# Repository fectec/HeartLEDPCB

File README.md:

# Heart LED PCB

<p align="justify">A collection of <b>Valentine's Day-themed PCB designs</b> featuring LED animations in the shape of a heart. Perfect for pendants or keyrings!</p>

## Main Branch

<p align="justify">The main branch features a design built around the <b>ICM7555</b> timer IC, configured in astable operation mode. The timer output drives a <b>CD4017B</b> decade counter, which sequences through LEDs to create an animated pattern. Power is supplied by a <b>CR2032</b> 3 V battery through a <b>TPS6122</b> boost converter.</p>

### Components Overview

#### ICM7555IBAZ-T

<p align="justify">The ICM7555 is a CMOS RC timer that provides significantly improved performance over the standard SE/NE 555/556 and 355 timers. It is a direct replacement for these devices in most applications. Enhanced features include low supply current (<i>60 μA</i>), a wide operating supply voltage range (<i>2V to 18V</i>), higher frequency performance, and no requirement to decouple the Control Voltage pin for stable operation.</p> 

<p align="justify">Although the ICM7555 itself consumes very little current, the total system supply current can increase unless high-impedance timing components are used. To address this, a high value for R and a low value for C were selected.</p> 

<p align="justify">The frequency of the astable operation is determined by the formula:</p> 

<div align="center">
	
$`f=\frac{1}{RC}`$

</div>

<p align="justify">To achieve a period of approximately one second, R was set to <i>100 kΩ</i> and C to <i>4.7 μF</i>.</p> 

#### CD4017BM96

<p align="justify">The CD4017B is a decade counter with 10 decoded outputs. Each output remains high for the duration of one full clock cycle, sequentially cycling through the outputs with each clock pulse. It operates over a wide supply voltage range of <i>3V to 18V</i>, making it compatible with various applications.</p>

#### TPS61222DCKR

<p align="justify">The TPS6122x family devices provide a power-supply solution for products powered by single-cell, two-cell, or three-cell alkaline, NiCd, or NiMH batteries, or a single-cell Li-Ion or Li-polymer battery. They offer up to 95% efficiency under typical operating conditions.</p>

<p align="justify">In this design, the specific application of the device is a fixed output voltage supply of <i>5 V at up to 60 mA</i>. The TPS61222 DC/DC converter is suitable for systems powered by a total typical input voltage between 0.7 V and 5.5 V.</p>

<p align="justify">In the fixed-voltage version, the output is set by an internal resistor divider. To ensure proper operation, a suitable inductor must be connected between pin VIN and pin L. Inductor values of <i>4.7 μH</i> provide good performance across the full input and output voltage range. Using inductor values below 2.2 μH is not recommended.</p>

<p align="justify">An input capacitor with a value of at least <i>10 μF</i> is recommended to improve the transient behavior of the regulator and reduce EMI in the total power supply circuit. A ceramic capacitor placed as close as possible to the VIN and GND pins of the IC is advised.</p>

<p align="justify">For the output capacitor (C2), small ceramic capacitors are recommended, placed as close as possible to the VOUT and GND pins of the IC. A minimum capacitance value of 4.7 μF should be used; <i>10 μF</i> is preferred.</p>

### BOM & Schematic Diagram

| Component   | Value/Model        | Qty | LCSC #      | Notes                          |
|-------------|--------------------|-----|-------------|--------------------------------|
| BT1         | Keystone 1060      | 1   | C5370859    | CR2032 holder                  |
| C1          | 4.7 µF             | 1   | C1705       | ICM7555 capacitor              | 
| C2, C3      | 10 µF              | 2   | C1691       | TPS61222 Input/output caps     |
| L1          | 4.7 µH             | 1   | C576538     | LQH3NPN series                 |
| R1          | 100 kΩ             | 1   | C15458      | Timer RC network               |
| R2          | 10 kΩ              | 1   | C25531      | Timer RC network               |
| R3-R12      | 3.3 kΩ             | 10  | C25936      | LED current limit              |
| U1          | ICM7555IBAZ-T      | 1   | C357816     | CMOS timer                     |
| U2          | CD4017BM96         | 1   | C11349      | Decade counter                 |
| U3          | TPS61222DCKR       | 1   | C116461     | Boost converter                |
| U4          | HX SS12F44G4       | 1   | C5149844    | Power switch                   |
| TP1-TP3     | 1.0 mm             | 3   | -           | Test points                    |

## HT7750A Branch

<p align="justify">In this branch, the TPS61222DCKR converter is replaced by the <b>HT7750A</b>. The HT77XXA series is a family of step-up DC/DC converters known for their high efficiency and low ripple. These converters feature an extremely low start-up voltage and high output voltage accuracy. They require only three external components to provide a fixed output voltage of 2.7 V, 3.0 V, 3.3 V, or <i>5.0 V</i>.</p>

### BOM & Schematic Diagram

| Component   | Value/Model        | Qty | LCSC #      | Notes                          |
|-------------|--------------------|-----|-------------|--------------------------------|
| BT1         | Keystone 1060      | 1   | C5370859    | CR2032 holder                  |
| C1          | 4.7 µF             | 1   | C1705       | ICM7555 capacitor              | 
| C2          | 47 µF (Tantalum)   | 1   | C7190       | HT7750A input capacitor        |
| C3          | 22 µF (Tantalum)   | 1   | C7183       | HT7750A output capacitor       |
| L1          | 47-100 µH          | 1   | C1034       | HT7750A inductor               |
| S1          | 1N5817             | 1   | C727113     | HT7750A schottky diode         |
| R1          | 100 kΩ             | 1   | C15458      | Timer RC network               |
| R2          | 10 kΩ              | 1   | C25531      | Timer RC network               |
| R3-R12      | 3.3 kΩ             | 10  | C25936      | LED current limit              |
| U1          | ICM7555IBAZ-T      | 1   | C357816     | CMOS timer                     |
| U2          | CD4017BM96         | 1   | C11349      | Decade counter                 |
| U3          | HT7750A            | 1   | C25988      | Boost converter                |
| U4          | HX SS12F44G4       | 1   | C5149844    | Power switch                   |
| TP1-TP3     | 1.0 mm             | 3   | -           | Test points                    |

## MCU Branch

<p align="justify">This branch replaces the timer and decade counter with an <b>ATtiny816</b> microcontroller. The ATtiny816 is a member of the tinyAVR® 1-series family featuring advanced analog features and core independent peripherals. This design allows for more sophisticated LED control and animations through programmable patterns.</p>

<p align="justify">Programming is accomplished via the Unified Program and Debug Interface (<i>UPDI</i>), a one-wire interface for external programming and debugging. The circuit incorporates a tactile button connected to a GPIO pin for user interaction.</p>

### BOM & Schematic Diagram

| Component   | Value/Model        | Qty | LCSC #      | Notes                          |
|-------------|--------------------|-----|-------------|--------------------------------|
| BT1         | CR2032-BS-6-1      | 1   | C70377      | CR2032 holder                  |
| C1          | 100 nF             | 2   | C301918     | MCU decoupling capacitors      |
| C2          | 100 nF             | 2   | C301918     | Button debounce capacitor      |
| D1          | LED (Blue)         | 1   | C7496819    | Status LED                     |
| D2-D10      | LED (Red)          | 9   | C7496820    | Animation LEDs                 |
| J1          | 1x03 2.54 mm       | 1   | -           | UPDI programming header        |
| R1-R11      | 1 kΩ               | 11  | C25543      | LED current limit              |
| SW1         | TS-1187A-B-A-B     | 1   | C318884     | Tactile switch                 |
| U1          | HX SS12F44G4       | 1   | C5149844    | Power switch                   |
| U2          | ATTINY816-MN       | 1   | C617908     | Main MCU                       |
| TP1         | 1.5 mm             | 1   | -           | Test point                     |

## Simple NE555 Branch

<p align="justify">Finally, this branch replaces the ICM7555 timer IC with a conventional <b>NE555</b>, offering a cost-effective alternative that requires only one SMD component - the IC itself. This design imitates a popular DIY kit, where the NE555 generates a <i>1 Hz signal</i> at pin 3, alternating between high and low levels. When pin 3 is low, the upper row of LEDs illuminates, and when high, the bottom row lights up instead, creating an appealing visual effect.</p>

<p align="justify">While the circuit can operate with a CR2032 3V battery, one LED row will appear dimmer due to the NE555's minimum voltage requirements. For optimal brightness across both rows, a 5V power supply connector can be soldered to the board as an alternative power source.</p>

### BOM & Schematic Diagram

| Component   | Value/Model                    | Qty | Notes                          |
|-------------|--------------------------------|-----|--------------------------------|
| U1          | NE555DR                        | 1   | RC Timer                       |
| U2          | 1066                           | 1   | CR2032 holder                  |
| SW1         | SS12D00G3                      | 1   | Power switch                   |
| D1-D10      | LED 3.00 mm                    | 10  | LEDs                           |
| R1-R10      | 1 kΩ 6.3 x 2.5 x 7.62 mm       | 10  | LED current limit              |
| R11-R12     | 10 kΩ 6.3 x 2.5 x 7.62 mm      | 2   | Timer RC network               |
| C1          | 47 µF 5.00 x 7.00 x 2.00 mm    | 1   | NE555 capacitor                |
| J1          | 1x02 2.54 mm                   | 1   | Power supply header            |

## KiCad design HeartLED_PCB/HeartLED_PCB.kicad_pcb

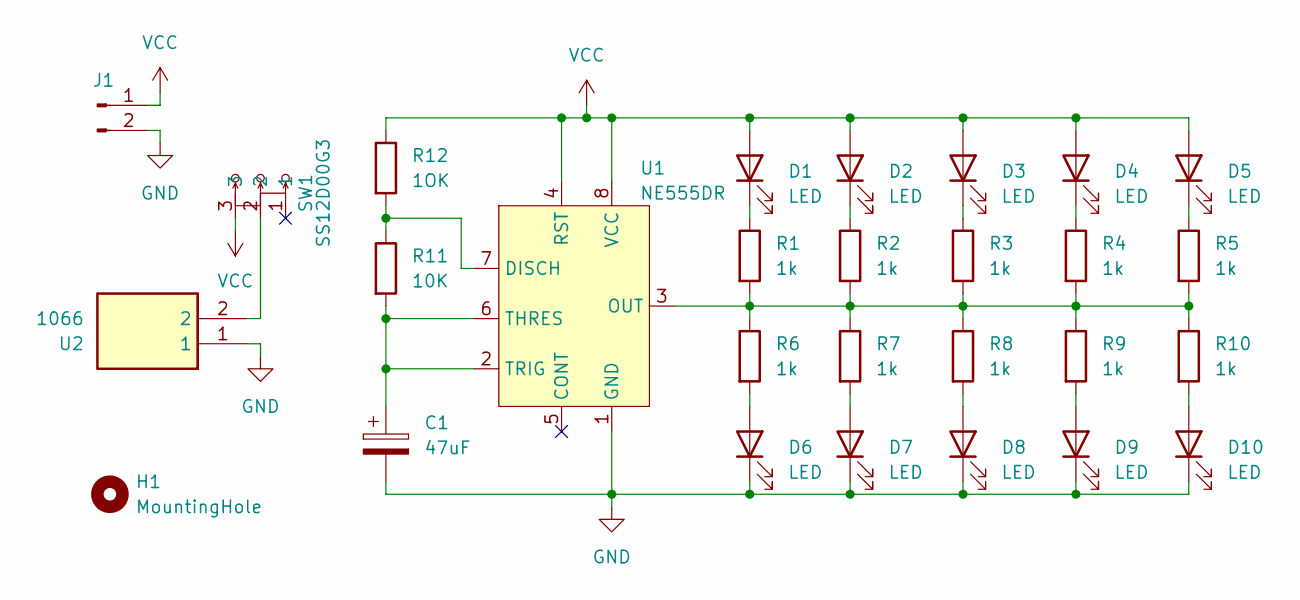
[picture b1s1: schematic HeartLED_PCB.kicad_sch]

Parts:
C1: 47uF; C_Radial_D5.0mm_H7.0mm_P2.00mm
D1, D2, D3, D4, D5, D6, D7, D8, D9, D10: LED; LED_D3.0mm
H1: MountingHole; MountingHole_2.7mm
J1: Conn_01x02_Pin; PinHeader_1x02_P2.54mm_Vertical
R1, R2, R3, R4, R5, R6, R7, R8, R9, R10: 1k; R_Axial_DIN0207_L6.3mm_D2.5mm_P7.62mm_Horizontal
R11: 10K; R_Axial_DIN0207_L6.3mm_D2.5mm_P7.62mm_Horizontal
R12: 1OK; R_Axial_DIN0207_L6.3mm_D2.5mm_P7.62mm_Horizontal
SW1: SS12D00G3; LCSC Part C9900018735
U1: NE555DR; LCSC Part C7593
U2: 1066; Mouser Part Number 534-1066

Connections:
GND: C1.2, D6.1 (K), D7.1 (K), D8.1 (K), D9.1 (K), D10.1 (K), J1.2, U1.1 (GND), U2.1
unnamed: D1.1 (K), R1.1
unnamed: D2.1 (K), R2.1
unnamed: D3.1 (K), R3.1
unnamed: D4.1 (K), R4.1
unnamed: D5.1 (K), R5.1
unnamed: D6.2 (A), R6.2
unnamed: D7.2 (A), R7.2
unnamed: D8.2 (A), R8.2
unnamed: D9.2 (A), R9.2
unnamed: D10.2 (A), R10.2
unnamed: SW1.2, U2.2
unnamed: R11.1, R12.2, U1.7 (DISCH)
unnamed: R1.2, R2.2, R3.2, R4.2, R5.2, R6.1, R7.1, R8.1, R9.1, R10.1, U1.3 (OUT)
unnamed: C1.1, R11.2, U1.2 (TRIG), U1.6 (THRES)
VCC: D1.2 (A), D2.2 (A), D3.2 (A), D4.2 (A), D5.2 (A), J1.1, R12.1, SW1.3, U1.4 (RST), U1.8 (VCC)

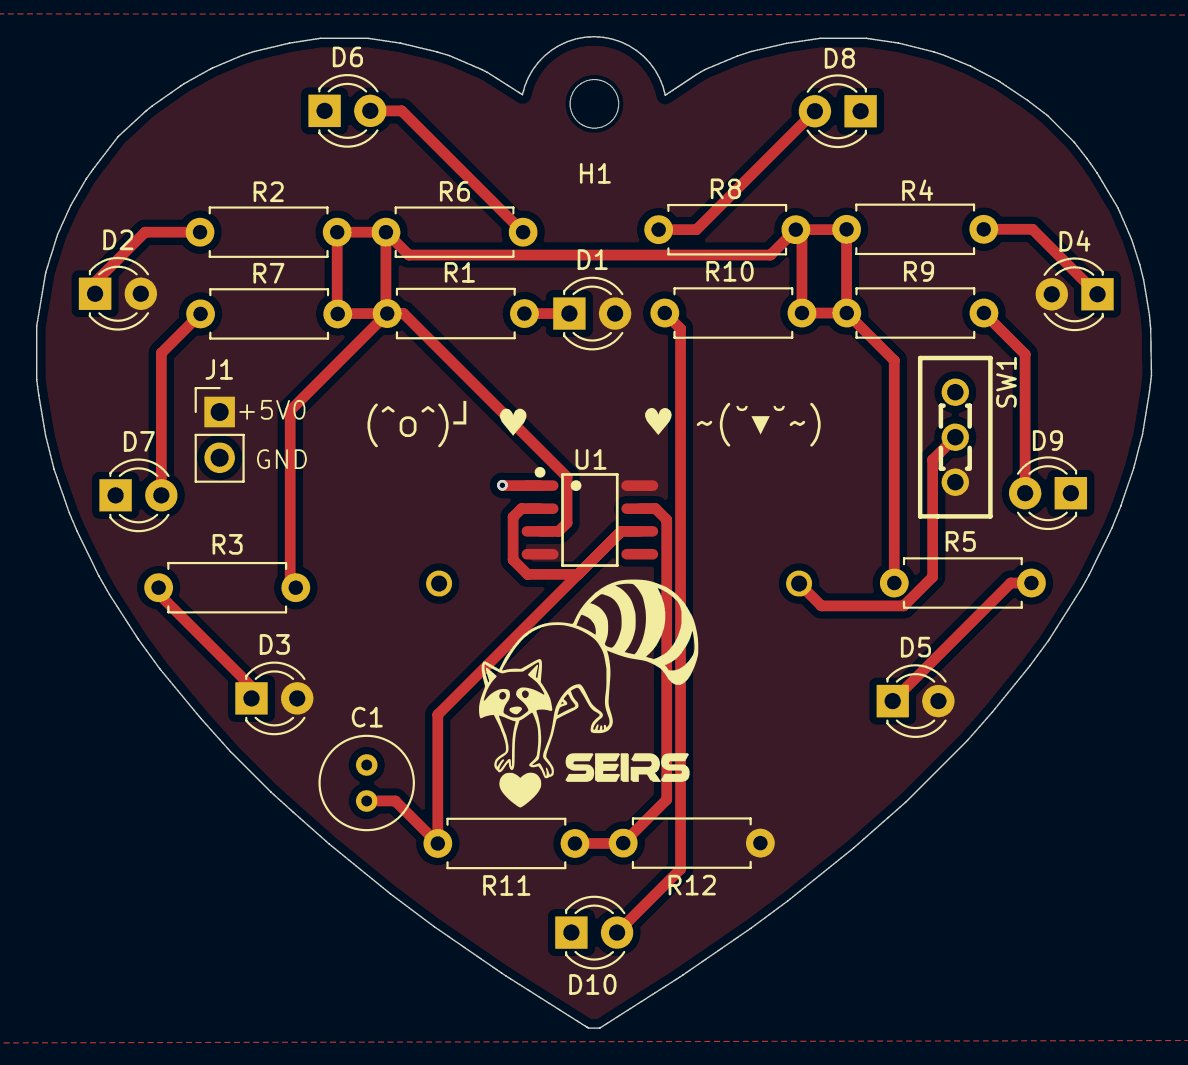
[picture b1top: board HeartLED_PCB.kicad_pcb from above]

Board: 2 copper layers, 61.9 x 55.1 mm, 28 parts (1 on the bottom side), 16 nets.

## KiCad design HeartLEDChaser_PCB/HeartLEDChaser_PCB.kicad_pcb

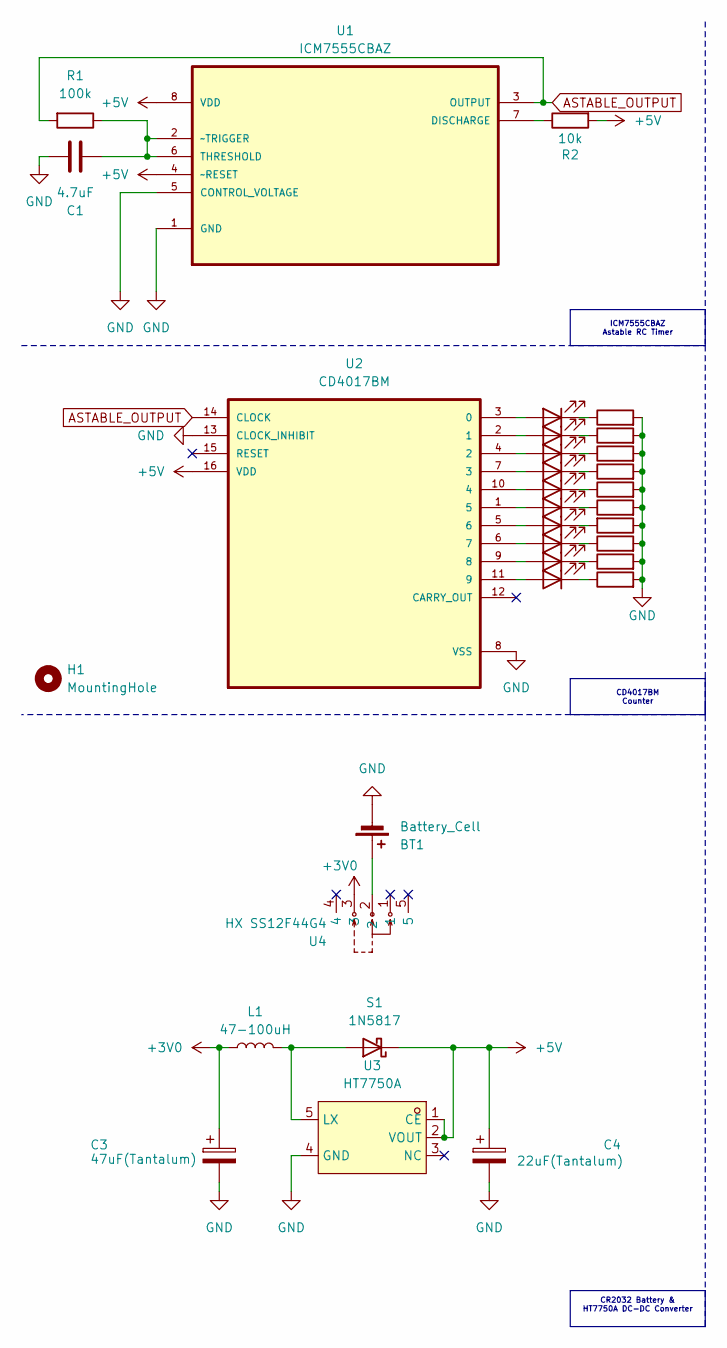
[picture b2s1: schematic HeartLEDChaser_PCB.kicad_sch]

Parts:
BT1: Battery_Cell; BatteryHolder_Keystone_1060_1x2032
C1: 4.7uF; CL10A475KP8NNNC
C3: 47uF(Tantalum); TAJA476K006RNJ
C4: 22uF(Tantalum); TAJA476K006RNJ
D1, D2, D3, D4, D5, D6, D7, D8, D9, D10: LED; LED_D3.0mm
H1: MountingHole; MountingHole_2.1mm
L1: 47-100uH; SDFL1608Q4R7KTF
R1: 100k; 0603WAJ0104T5E
R2: 10k; 0402WGJ0103TCE
R3, R4, R5, R6, R7, R8, R9, R10, R11, R12: 3.3k; 0402WGJ0332TCE
S1: 1N5817; 1N5817W
U1: ICM7555CBAZ; MPN ICM7555CBAZ
U2: CD4017BM
U3: HT7750A; LCSC Part C259884
U4: HX SS12F44G4; LCSC Part C5149844

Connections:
+3V0: C3.1, L1.1, U4.3
+5V: C4.1, R2.2, S1.1 (K), U1.4 (~RESET), U1.8 (VDD), U2.16 (VDD), U3.1 (CE), U3.2 (VOUT)
ASTABLE_OUTPUT: R1.2, U1.3 (OUTPUT), U2.14 (CLOCK)
GND: BT1.2 (-), C1.2, C3.2, C4.2, R3.2, R4.2, R5.2, R6.2, R7.1, R8.2, R9.2, R10.2, R11.2, R12.2, U1.1 (GND), U1.5 (CONTROL_VOLTAGE), U2.8 (VSS), U2.13 (CLOCK_INHIBIT), U3.4 (GND)
unnamed: BT1.1 (+), U4.2
unnamed: D1.2 (A), U2.1 (5)
unnamed: D1.1 (K), R3.1
unnamed: D2.2 (A), U2.2 (1)
unnamed: D2.1 (K), R4.1
unnamed: D3.2 (A), U2.3 (0)
unnamed: D3.1 (K), R5.1
unnamed: D4.2 (A), U2.4 (2)
unnamed: D4.1 (K), R6.1
unnamed: D5.2 (A), U2.5 (6)
unnamed: D5.1 (K), R7.2
unnamed: D6.2 (A), U2.6 (7)
unnamed: D6.1 (K), R8.1
unnamed: D7.2 (A), U2.7 (3)
unnamed: D7.1 (K), R9.1
unnamed: D8.2 (A), U2.9 (8)
unnamed: D8.1 (K), R10.1
unnamed: D9.2 (A), U2.10 (4)
unnamed: D9.1 (K), R11.1
unnamed: D10.2 (A), U2.11 (9)
unnamed: D10.1 (K), R12.1
unnamed: L1.2, S1.2 (A), U3.5 (LX)
unnamed: R2.1, U1.7 (DISCHARGE)
unnamed: C1.1, R1.1, U1.2 (~TRIGGER), U1.6 (THRESHOLD)

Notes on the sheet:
CR2032 Battery & HT7750A DC-DC Converter
CD4017BM Counter
ICM7555CBAZ Astable RC Timer

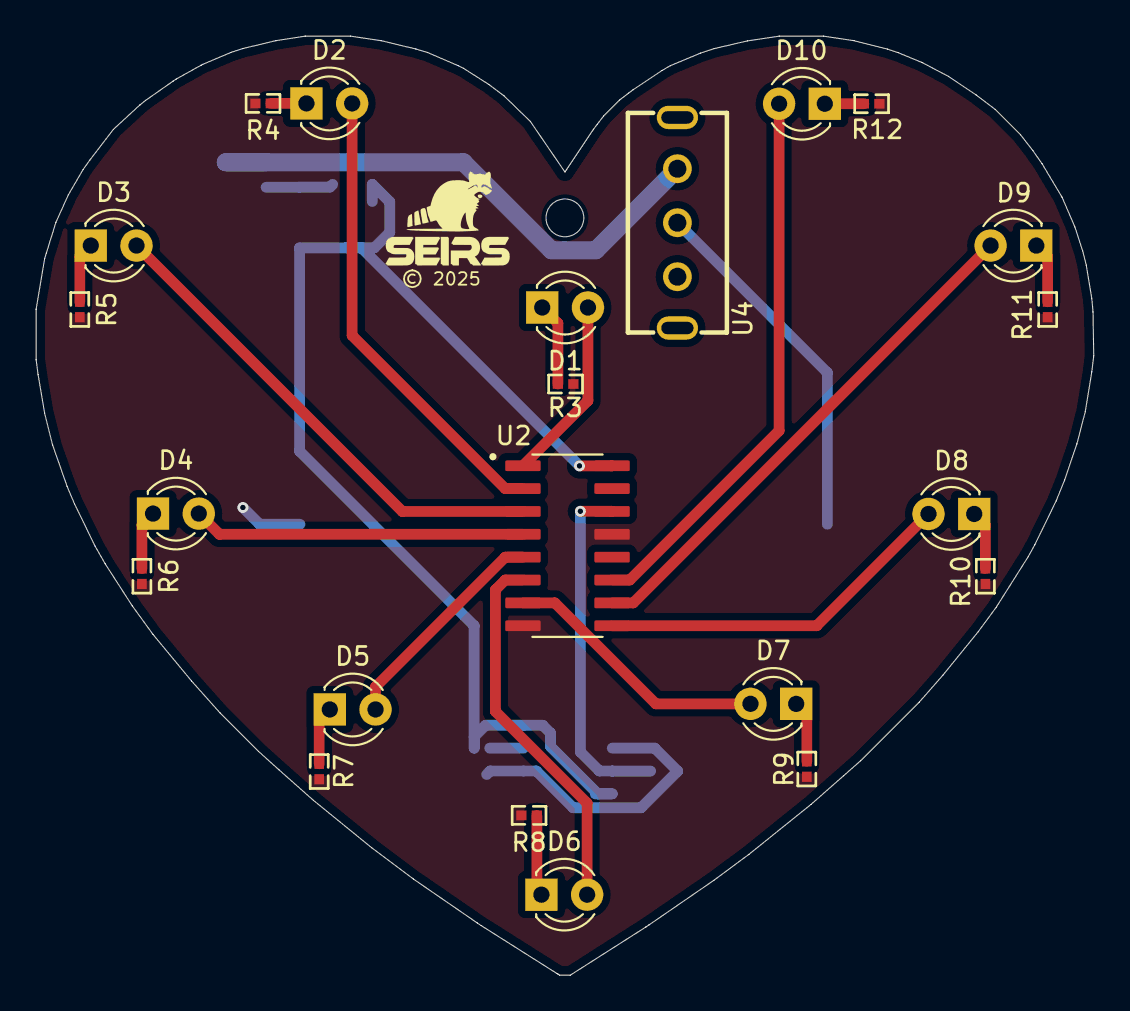
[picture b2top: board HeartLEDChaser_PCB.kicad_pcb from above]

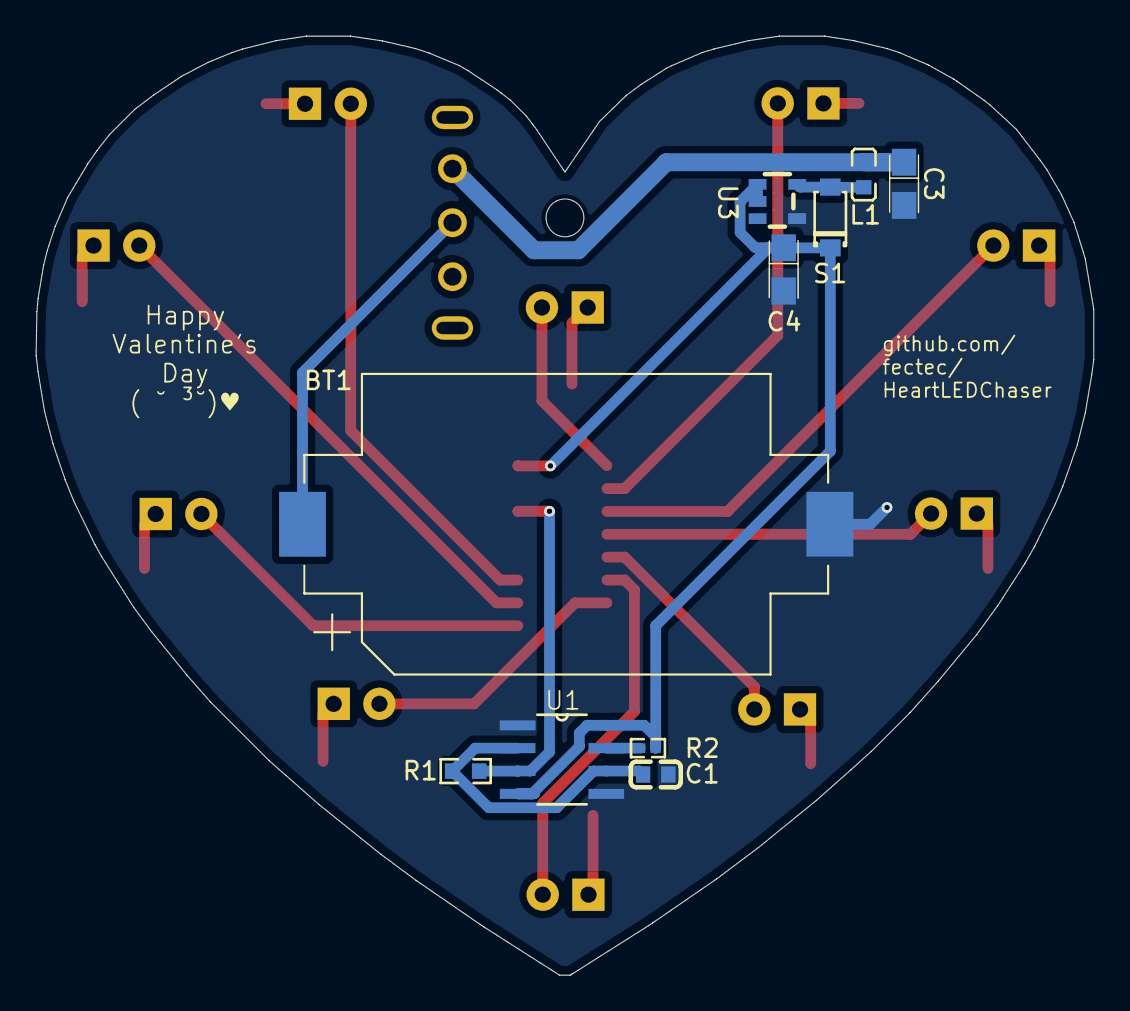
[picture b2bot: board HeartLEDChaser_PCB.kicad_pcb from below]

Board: 2 copper layers, 58.8 x 52.2 mm, 33 parts (10 on the bottom side), 28 nets.

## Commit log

2025-01-10 .gitignore applied
2025-01-10 Routed PCB
2025-01-10 Added logos
2025-01-10 Improved layout & routing
2025-01-10 Cleanup
2025-01-10 Corrected capacitor references
2025-01-10 Renamed project
2025-01-11 Added LCSC and 3D models
2025-01-11 Changed inductor
2025-01-11 Added TestPoints and corrected track width for power nets
2025-01-11 Changed Timer and Counter models
2025-01-11 Added some 3D models
2025-01-11 Changed DC-DC Boost Converter
2025-01-15 Fixed local libraries
2025-01-16 Ready to route
2025-01-16 Added silkscreen logos
2025-01-18 Routing done
2025-06-01 docs: update README.md

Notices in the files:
HeartLEDChaser_PCB/HeartLEDChaser_PCB.kicad_pcb:
© 2025
